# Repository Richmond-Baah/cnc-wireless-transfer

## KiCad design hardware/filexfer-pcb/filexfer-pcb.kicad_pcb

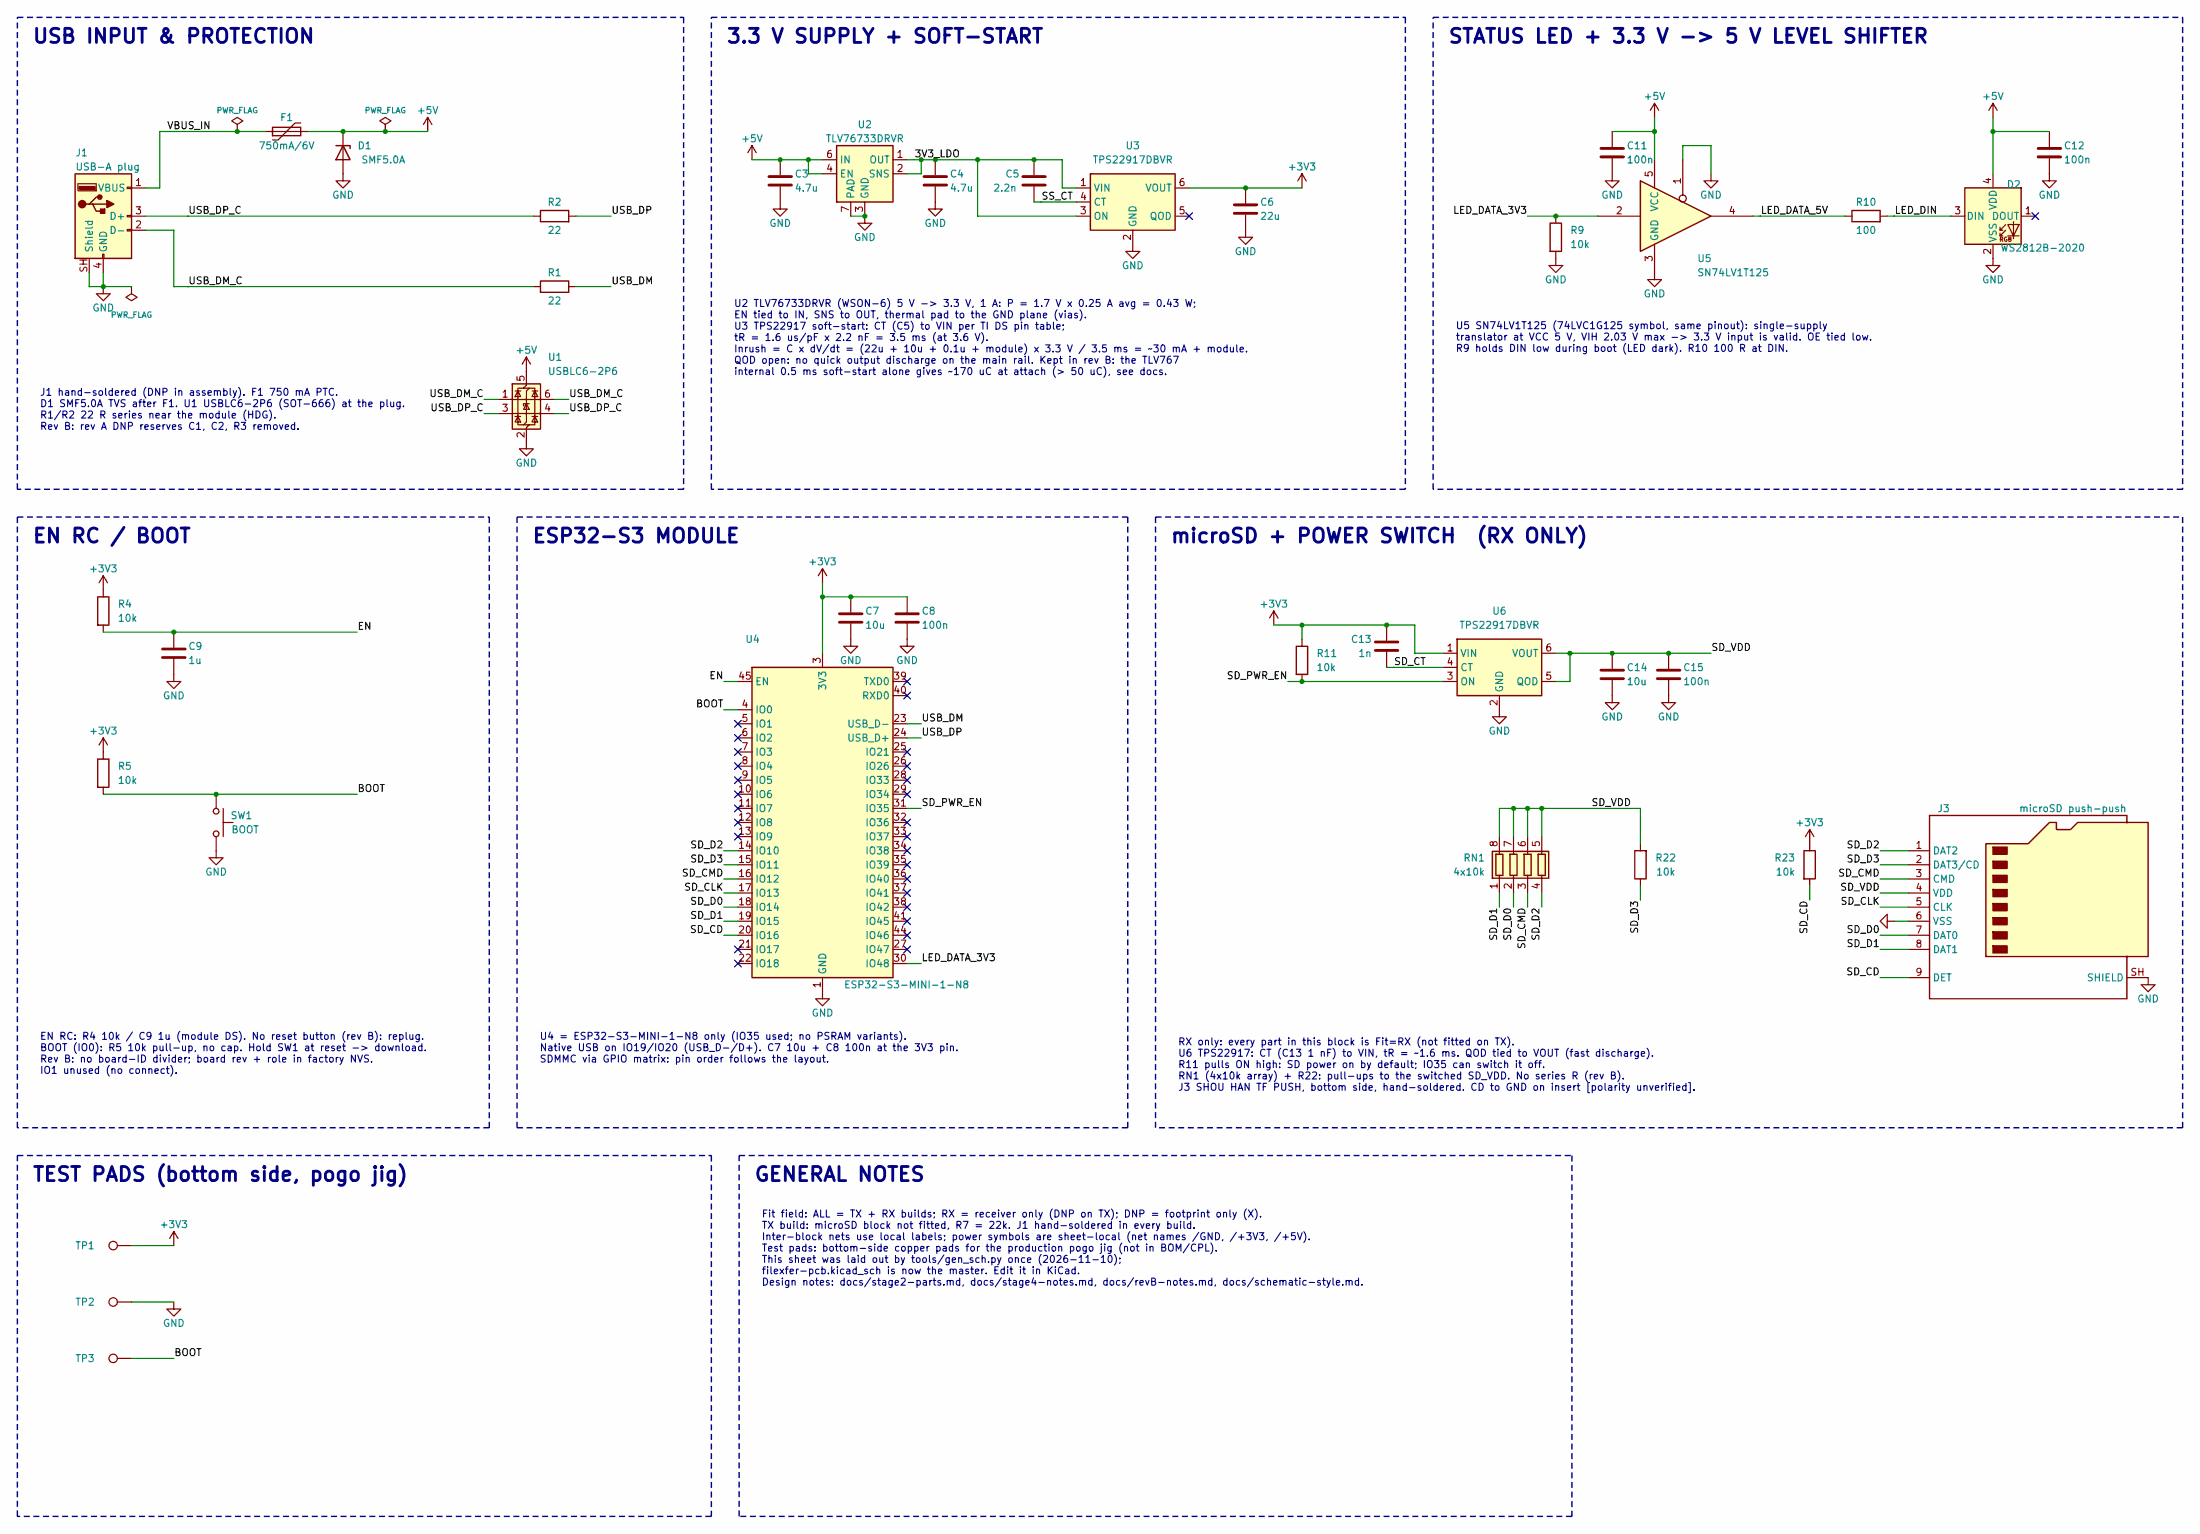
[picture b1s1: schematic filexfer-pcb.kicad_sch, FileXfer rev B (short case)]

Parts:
C3, C4: 4.7u; C_0603_1608Metric; MPN CL10A475KO8NNNC; LCSC C19666
C5: 2.2n; C_0402_1005Metric; MPN 0402B222K500NT; LCSC C1531
C6: 22u; C_0603_1608Metric; MPN CL10A226MQ8NRNC; LCSC C59461
C7, C14: 10u; C_0402_1005Metric; MPN CL05A106MQ5NUNC; LCSC C15525
C8, C11, C12, C15: 100n; C_0402_1005Metric; MPN CL05B104KO5NNNC; LCSC C1525
C9: 1u; C_0402_1005Metric; MPN CL05A105KA5NQNC; LCSC C52923
C13: 1n; C_0402_1005Metric; MPN 0402B102K500NT; LCSC C1523
D1: SMF5.0A; D_SMF; MPN SMF5.0A (Leiditech); LCSC C2759874
D2: WS2812B-2020; LED_WS2812B-2020_PLCC4_2.0x2.0mm; MPN WS2812B-2020-V6; LCSC C52917434
F1: 750mA/6V; Fuse_1206_3216Metric; MPN BSMD1206-075-6V; LCSC C883127
J1: USB-A plug; USB_A_Plug_XKB_U217-041N-4BV81; MPN U217-041N-4BV81; LCSC C319178
J3: microSD push-push; microSD_SHOUHAN_TF_PUSH; MPN TF PUSH (SHOU HAN); LCSC C393941
R1, R2: 22; R_0402_1005Metric; MPN 0402WGF220JTCE; LCSC C25092
R4, R5, R9, R11, R22, R23: 10k; R_0402_1005Metric; MPN 0402WGF1002TCE; LCSC C25744
R10: 100; R_0402_1005Metric; MPN 0402WGF1000TCE; LCSC C25076
RN1: 4x10k; R_Array_Convex_4x0402; MPN 4D02WGJ0103TCE; LCSC C25725
SW1: BOOT; SW_SPST_TS-1088-xR020; MPN TS-1088-AR02016; LCSC C720477
TP1: +3V3; TestPoint_Pad_D1.0mm; MPN pad
TP2: GND; TestPoint_Pad_D1.0mm; MPN pad
TP3: BOOT; TestPoint_Pad_D1.0mm; MPN pad
U1: USBLC6-2P6; SOT-666; MPN USBLC6-2P6; LCSC C15999
U2: TLV76733DRVR; WSON-6-1EP_2x2mm_P0.65mm_EP1x1.6mm; MPN TLV76733DRVR; LCSC C2848334
U3, U6: TPS22917DBVR; SOT-23-6; MPN TPS22917DBVR; LCSC C2681320
U4: ESP32-S3-MINI-1-N8; ESP32-S3-MINI-1; MPN ESP32-S3-MINI-1-N8; LCSC C2913206
U5: SN74LV1T125; SOT-353_SC-70-5; MPN SN74LV1T125DCKR; LCSC C75925

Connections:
/3V3_LDO: C4.1, C5.2, U2.1 (OUT), U2.2 (SNS), U3.1 (VIN), U3.3 (ON)
/+3V3: C6.1, C7.1, C8.1, C13.2, R4.1, R5.1, R11.1, R23.1, TP1.1, U3.6 (VOUT), U4.3 (3V3), U6.1 (VIN)
/+5V: C3.1, C11.1, C12.1, D1.1 (K), D2.4 (VDD), F1.2, U1.5 (VBUS), U2.4 (EN), U2.6 (IN), U5.5 (VCC)
/BOOT: R5.2, SW1.1, TP3.1, U4.4 (IO0)
/EN: C9.1, R4.2, U4.45 (EN)
/GND: C3.2, C4.2, C6.2, C7.2, C8.2, C9.2, C11.2, C12.2, C14.2, C15.2, D1.2 (A), D2.2 (VSS), J1.4 (GND), J1.SH (Shield), J3.6 (VSS), J3.SH (SHIELD), R9.2, SW1.2, TP2.1, U1.2 (GND), U2.3 (GND), U2.5 (GND), U2.7 (PAD), U3.2 (GND), U4.1 (GND), U4.2 (GND), U4.42 (GND), U4.43 (GND), U4.46 (GND), U4.47 (GND), U4.48 (GND), U4.49 (GND), U4.50 (GND), U4.51 (GND), U4.52 (GND), U4.53 (GND), U4.54 (GND), U4.55 (GND), U4.56 (GND), U4.57 (GND), U4.58 (GND), U4.59 (GND), U4.60 (GND), U4.61 (GND), U4.62 (GND), U4.63 (GND), U4.64 (GND), U4.65 (GND), U5.1, U5.3 (GND), U6.2 (GND)
/LED_DATA_3V3: R9.1, U4.30 (IO48), U5.2
/LED_DATA_5V: R10.1, U5.4
/LED_DIN: D2.3 (DIN), R10.2
/SD_CD: J3.9 (DET), R23.2, U4.20 (IO16)
/SD_CLK: J3.5 (CLK), U4.17 (IO13)
/SD_CMD: J3.3 (CMD), RN1.3 (R3.1), U4.16 (IO12)
/SD_CT: C13.1, U6.4 (CT)
/SD_D0: J3.7 (DAT0), RN1.2 (R2.1), U4.18 (IO14)
/SD_D1: J3.8 (DAT1), RN1.1 (R1.1), U4.19 (IO15)
/SD_D2: J3.1 (DAT2), RN1.4 (R4.1), U4.14 (IO10)
/SD_D3: J3.2 (DAT3/CD), R22.1, U4.15 (IO11)
/SD_PWR_EN: R11.2, U4.31 (IO35), U6.3 (ON)
/SD_VDD: C14.1, C15.1, J3.4 (VDD), R22.2, RN1.5 (R4.2), RN1.6 (R3.2), RN1.7 (R2.2), RN1.8 (R1.2), U6.5 (QOD), U6.6 (VOUT)
/SS_CT: C5.1, U3.4 (CT)
/USB_DM: R1.2, U4.23 (USB_D-)
/USB_DM_C: J1.2 (D-), R1.1, U1.1 (I/O1), U1.6 (I/O1)
/USB_DP: R2.2, U4.24 (USB_D+)
/USB_DP_C: J1.3 (D+), R2.1, U1.3 (I/O2), U1.4 (I/O2)
/VBUS_IN: F1.1, J1.1 (VBUS)

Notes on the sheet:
USB INPUT & PROTECTION
3.3 V SUPPLY + SOFT-START
STATUS LED + 3.3 V -> 5 V LEVEL SHIFTER
EN RC / BOOT
ESP32-S3 MODULE
microSD + POWER SWITCH (RX ONLY)
TEST PADS (bottom side, pogo jig)
GENERAL NOTES
J1 hand-soldered (DNP in assembly). F1 750 mA PTC. D1 SMF5.0A TVS after F1. U1 USBLC6-2P6 (SOT-666) at the plug. R1/R2 22 R series near the module (HDG). Rev B: rev A DNP reserves C1, C2, R3 removed.
U2 TLV76733DRVR (WSON-6) 5 V -> 3.3 V, 1 A: P = 1.7 V x 0.25 A avg = 0.43 W; EN tied to IN, SNS to OUT, thermal pad to the GND plane (vias). U3 TPS22917 soft-start: CT (C5) to VIN per TI DS pin table; tR = 1.6 us/pF x 2.2 nF = 3.5 ms (at 3.6 V). Inrush = C x dV/dt = (22u + 10u + 0.1u + module) x 3.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
U5 SN74LV1T125 (74LVC1G125 symbol, same pinout): single-supply translator at VCC 5 V, VIH 2.03 V max -> 3.3 V input is valid. OE tied low. R9 holds DIN low during boot (LED dark). R10 100 R at DIN.
EN RC: R4 10k / C9 1u (module DS). No reset button (rev B): replug. BOOT (IO0): R5 10k pull-up, no cap. Hold SW1 at reset -> download. Rev B: no board-ID divider; board rev + role in factory NVS. IO1 unused (no connect).
U4 = ESP32-S3-MINI-1-N8 only (IO35 used; no PSRAM variants). Native USB on IO19/IO20 (USB_D-/D+). C7 10u + C8 100n at the 3V3 pin. SDMMC via GPIO matrix: pin order follows the layout.
RX only: every part in this block is Fit=RX (not fitted on TX). U6 TPS22917: CT (C13 1 nF) to VIN, tR = ~1.6 ms. QOD tied to VOUT (fast discharge). R11 pulls ON high: SD power on by default; IO35 can switch it off. RN1 (4x10k array) + R22: pull-ups to the switched SD_VDD. No series R (rev B). J3 SH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
Fit field: ALL = TX + RX builds; RX = receiver only (DNP on TX); DNP = footprint only (X). TX build: microSD block not fitted, R7 = 22k. J1 hand-soldered in every build. Inter-block nets use local labels; power symbols are sheet-local (net names /GND, /+3V3, /+5V). Test pads: bottom-side copper pad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

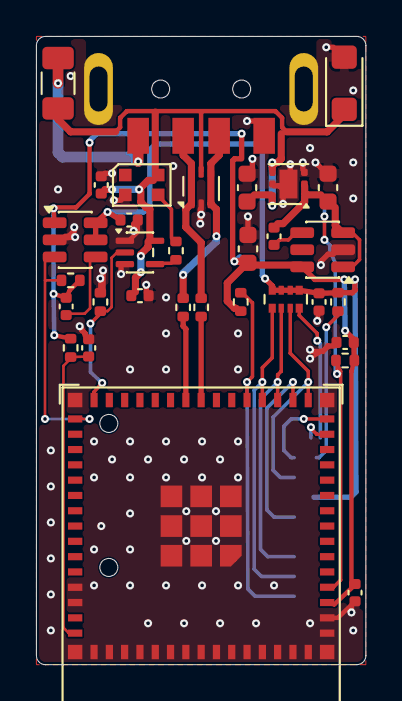
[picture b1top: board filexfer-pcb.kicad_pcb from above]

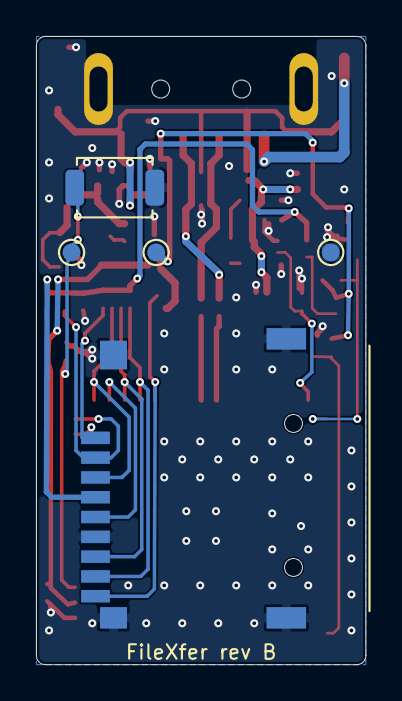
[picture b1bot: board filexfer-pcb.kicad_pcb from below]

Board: 2 copper layers, 18.3 x 34.9 mm, 37 parts (5 on the bottom side), 25 nets.

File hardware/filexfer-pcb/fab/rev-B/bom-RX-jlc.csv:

Comment,Designator,Footprint,LCSC Part #,MPN,Qty
4.7u,"C3,C4",C_0603_1608Metric,C19666,CL10A475KO8NNNC,2
2.2n,C5,C_0402_1005Metric,C1531,0402B222K500NT,1
22u,C6,C_0603_1608Metric,C59461,CL10A226MQ8NRNC,1
10u,"C7,C14",C_0402_1005Metric,C15525,CL05A106MQ5NUNC,2
100n,"C8,C11,C12,C15",C_0402_1005Metric,C1525,CL05B104KO5NNNC,4
1u,C9,C_0402_1005Metric,C52923,CL05A105KA5NQNC,1
1n,C13,C_0402_1005Metric,C1523,0402B102K500NT,1
SMF5.0A,D1,D_SMF,C2759874,SMF5.0A (Leiditech),1
WS2812B-2020,D2,LED_WS2812B-2020_PLCC4_2.0x2.0mm,C52917434,WS2812B-2020-V6,1
750mA/6V,F1,Fuse_1206_3216Metric,C883127,BSMD1206-075-6V,1
22,"R1,R2",R_0402_1005Metric,C25092,0402WGF220JTCE,2
10k,"R4,R5,R9,R11,R22,R23",R_0402_1005Metric,C25744,0402WGF1002TCE,6
100,R10,R_0402_1005Metric,C25076,0402WGF1000TCE,1
4x10k,RN1,R_Array_Convex_4x0402,C25725,4D02WGJ0103TCE,1
USBLC6-2P6,U1,SOT-666,C15999,USBLC6-2P6,1
TLV76733DRVR,U2,WSON-6-1EP_2x2mm_P0.65mm_EP1x1.6mm,C2848334,TLV76733DRVR,1
TPS22917DBVR,"U3,U6",SOT-23-6,C2681320,TPS22917DBVR,2
ESP32-S3-MINI-1-N8,U4,ESP32-S3-MINI-1,C2913206,ESP32-S3-MINI-1-N8,1
SN74LV1T125,U5,SOT-353_SC-70-5,C75925,SN74LV1T125DCKR,1

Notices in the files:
parts and their libraries:
ESP32-S3-MINI-1, from github.com/espressif/kicad-libraries (CC-BY-SA 4.0 with design exception). Pads checked against DS v1.7 Fig 11-1; antenna keepout 15.4 x 5.1 mm all layers
